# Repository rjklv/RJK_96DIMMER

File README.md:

# RJK_96DIMMER
Propeller based DMX 96 channel incandescent lamp dimmer

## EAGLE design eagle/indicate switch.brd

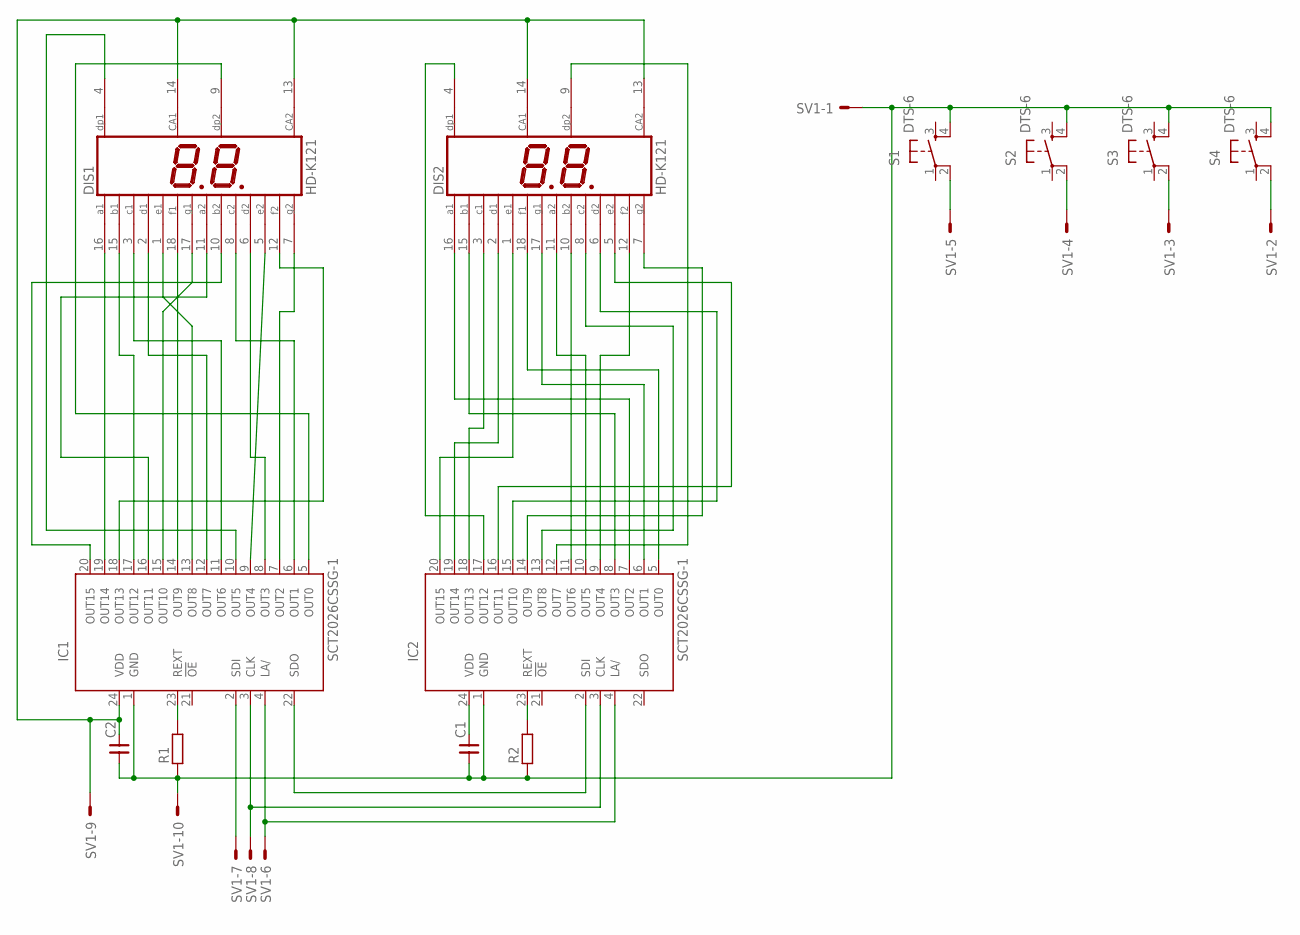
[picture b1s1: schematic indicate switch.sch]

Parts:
C1, C2: CNP-0805; 0805
DIS1, DIS2: HD-K121; HDSP-R
IC1, IC2: SCT2026CSSG-1; SSOP24
R1, R2: RESISTOR_0805; RESC2012X70N
S1, S2, S3, S4: DTS-6
SV1: ML10E; ML10

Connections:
unnamed: S2.2, SV1.4
unnamed: S1.2, SV1.5
unnamed: S4.2, SV1.2
unnamed: IC1.2 (SDI), SV1.7
unnamed: C1.1, C2.1, IC1.1 (GND), IC2.1 (GND), R1.1, R2.1, S1.4, S2.4, S3.4, S4.4, SV1.1, SV1.10
unnamed: C2.2, DIS1.13 (CA2), DIS1.14 (CA1), DIS2.13 (CA2), DIS2.14 (CA1), IC1.24 (VDD), SV1.9
unnamed: C1.2, IC2.24 (VDD)
unnamed: DIS1.15 (B1), IC1.17 (OUT12)
unnamed: IC1.23 (REXT), R1.2
unnamed: IC2.23 (REXT), R2.2
unnamed: S3.2, SV1.3
unnamed: IC1.3 (CLK), IC2.3 (CLK), SV1.8
unnamed: IC1.4 (LA/), IC2.4 (LA/), SV1.6
unnamed: IC1.22 (SDO), IC2.2 (SDI)
unnamed: DIS1.9 (DP2), IC1.5 (OUT0)
unnamed: DIS1.8 (C2), IC1.6 (OUT1)
unnamed: DIS1.7 (G2), IC1.7 (OUT2)
unnamed: DIS1.6 (D2), IC1.8 (OUT3)
unnamed: DIS1.5 (E2), IC1.9 (OUT4)
unnamed: DIS1.4 (DP1), IC1.10 (OUT5)
unnamed: DIS1.3 (C1), IC1.11 (OUT6)
unnamed: DIS1.2 (D1), IC1.12 (OUT7)
unnamed: DIS1.1 (E1), IC1.13 (OUT8)
unnamed: DIS1.18 (F1), IC1.14 (OUT9)
unnamed: DIS1.17 (G1), IC1.15 (OUT10)
unnamed: DIS1.16 (A1), IC1.16 (OUT11)
unnamed: DIS1.12 (F2), IC1.18 (OUT13)
unnamed: DIS1.11 (A2), IC1.19 (OUT14)
unnamed: DIS1.10 (B2), IC1.20 (OUT15)
unnamed: DIS2.18 (F1), IC2.5 (OUT0)
unnamed: DIS2.17 (G1), IC2.6 (OUT1)
unnamed: DIS2.16 (A1), IC2.7 (OUT2)
unnamed: DIS2.15 (B1), IC2.8 (OUT3)
unnamed: DIS2.12 (F2), IC2.9 (OUT4)
unnamed: DIS2.11 (A2), IC2.10 (OUT5)
unnamed: DIS2.10 (B2), IC2.11 (OUT6)
unnamed: DIS2.9 (DP2), IC2.12 (OUT7)
unnamed: DIS2.8 (C2), IC2.13 (OUT8)
unnamed: DIS2.7 (G2), IC2.14 (OUT9)
unnamed: DIS2.6 (D2), IC2.15 (OUT10)
unnamed: DIS2.5 (E2), IC2.16 (OUT11)
unnamed: DIS2.4 (DP1), IC2.17 (OUT12)
unnamed: DIS2.3 (C1), IC2.18 (OUT13)
unnamed: DIS2.2 (D1), IC2.19 (OUT14)
unnamed: DIS2.1 (E1), IC2.20 (OUT15)

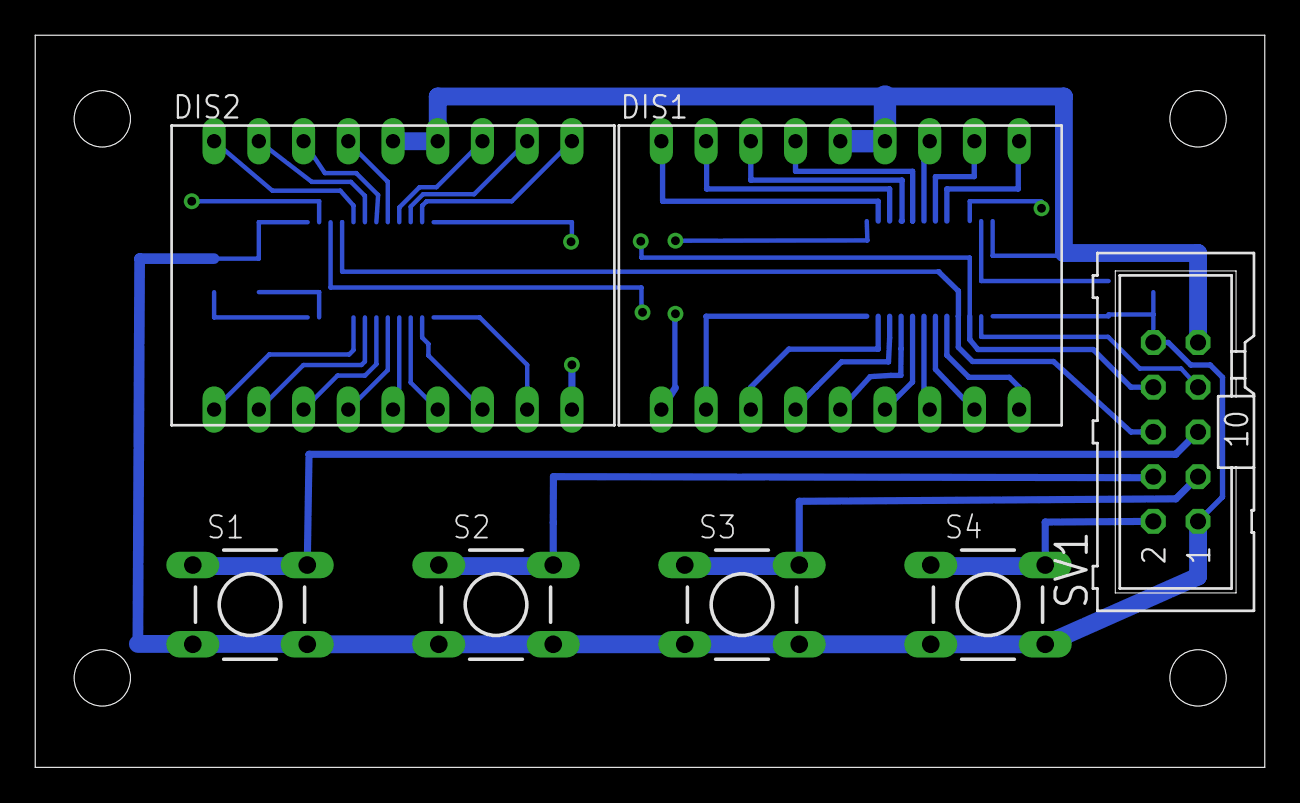
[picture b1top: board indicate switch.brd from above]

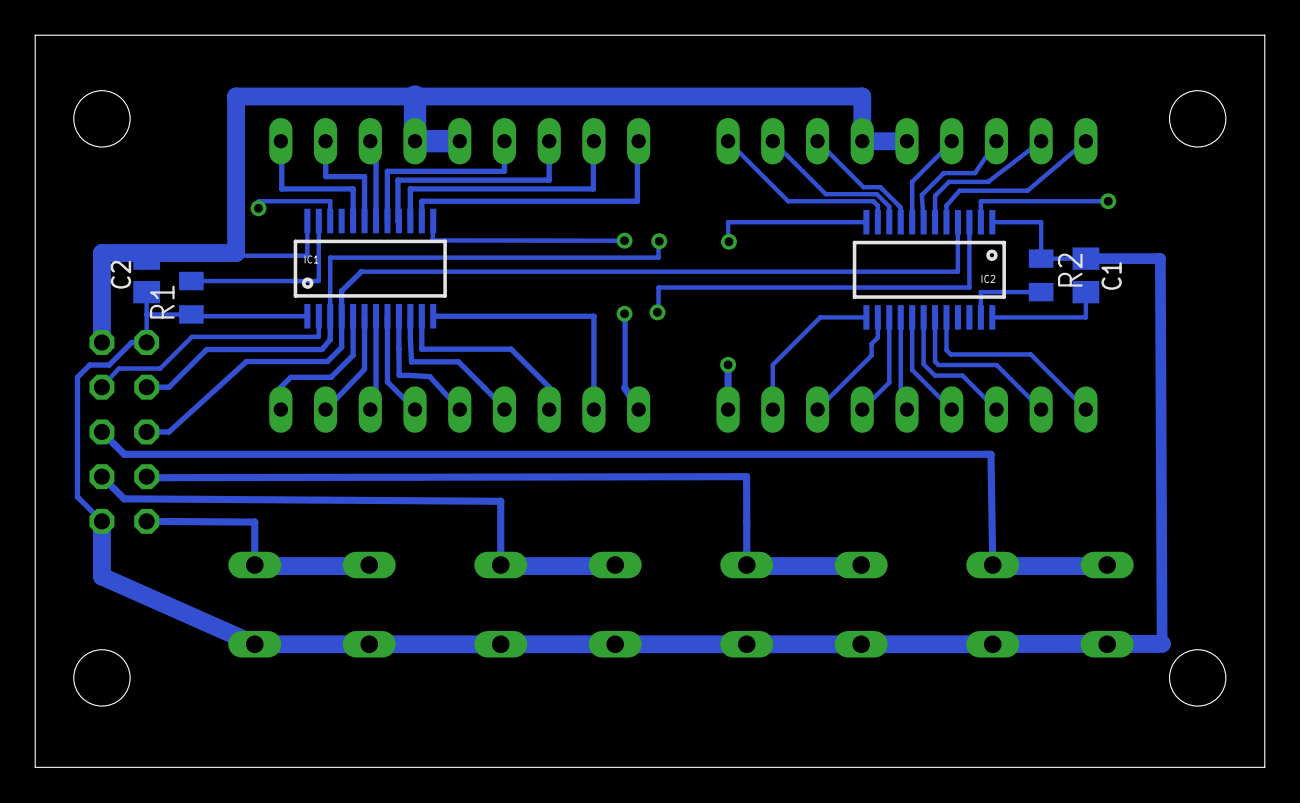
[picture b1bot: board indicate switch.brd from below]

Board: 2 copper layers, 69.8 x 41.6 mm, 13 parts (6 on the bottom side), 45 nets.

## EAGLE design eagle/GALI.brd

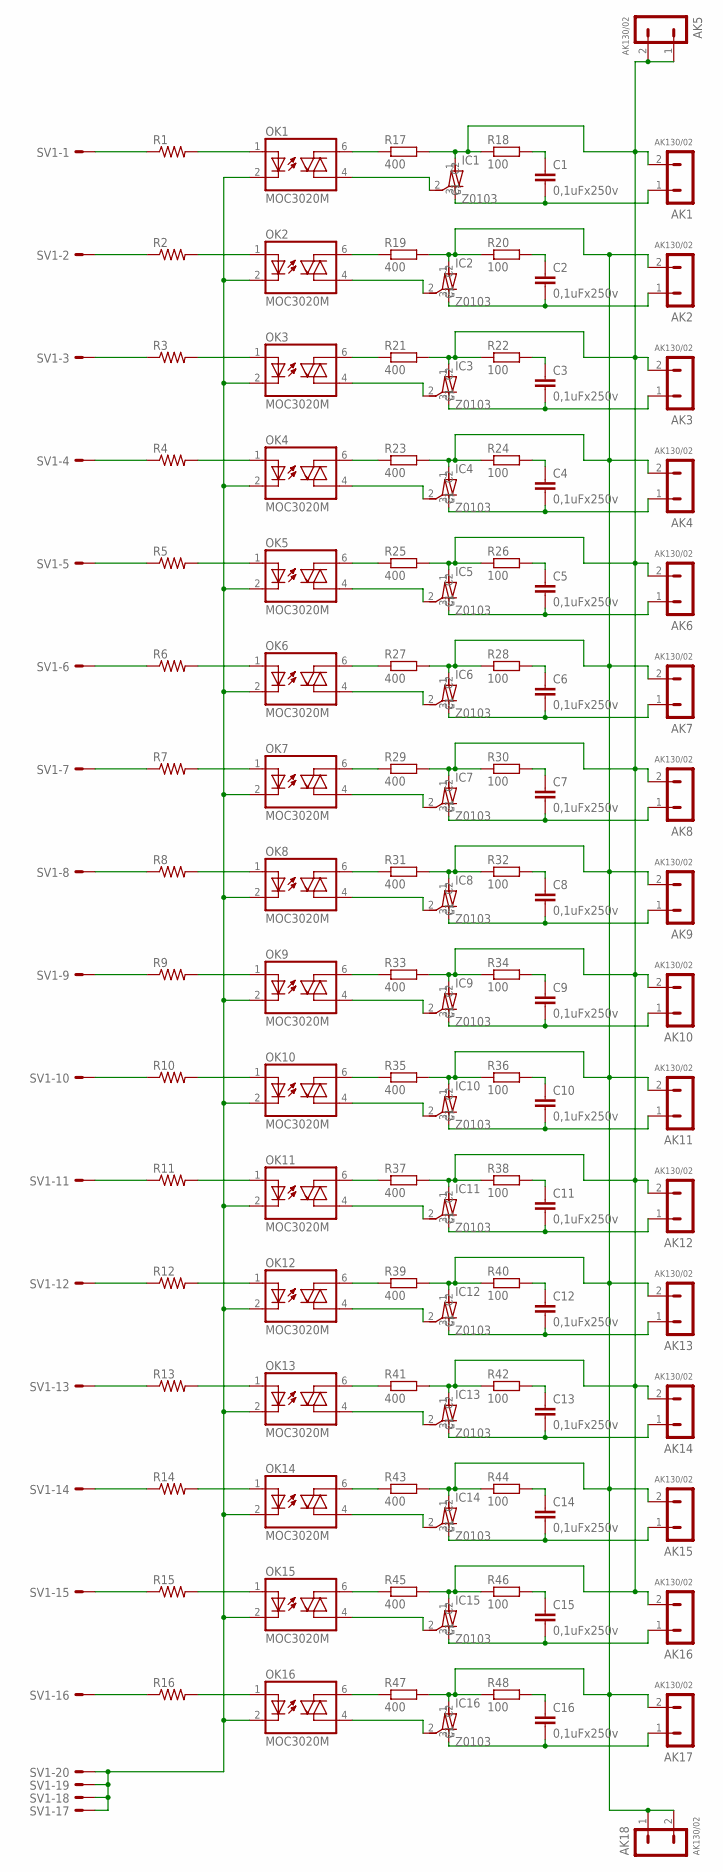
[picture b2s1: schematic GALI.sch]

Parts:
AK1, AK2, AK3, AK4, AK5, AK6, AK7, AK8, AK9, AK10, AK11, AK12, AK13, AK14, AK15, AK16, AK17, AK18: AK130/02; AK02
C1, C2, C3, C4, C5, C6, C7, C8, C9, C10, C11, C12, C13, C14, C15, C16: 0,1uFx250v; C102-054X133
IC1, IC2, IC3, IC4, IC5, IC6, IC7, IC8, IC9, IC10, IC11, IC12, IC13, IC14, IC15, IC16: Z0103; TO92-
OK1, OK2, OK3, OK4, OK5, OK6, OK7, OK8, OK9, OK10, OK11, OK12, OK13, OK14, OK15, OK16: MOC3020M; DIL06
R1, R2, R3, R4, R5, R6, R7, R8, R9, R10, R11, R12, R13, R14, R15, R16: R-US_0207/12; 0207/12
R17, R19, R21, R23, R25, R27, R29, R31, R33, R35, R37, R39, R41, R43, R45, R47: 400; P0613/15
R18, R20, R22, R24, R26, R28, R30, R32, R34, R36, R38, R40, R42, R44, R46, R48: 100; P0613/15
SV1: ML20E; ML20

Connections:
unnamed: R1.1, SV1.1
unnamed: OK2.1 (A), R2.2
unnamed: OK3.1 (A), R3.2
unnamed: OK4.1 (A), R4.2
unnamed: OK5.1 (A), R5.2
unnamed: OK6.1 (A), R6.2
unnamed: OK7.1 (A), R7.2
unnamed: OK8.1 (A), R8.2
unnamed: OK9.1 (A), R9.2
unnamed: OK10.1 (A), R10.2
unnamed: OK11.1 (A), R11.2
unnamed: OK12.1 (A), R12.2
unnamed: OK13.1 (A), R13.2
unnamed: OK14.1 (A), R14.2
unnamed: OK15.1 (A), R15.2
unnamed: R2.1, SV1.2
unnamed: OK1.2 (C), OK2.2 (C), OK3.2 (C), OK4.2 (C), OK5.2 (C), OK6.2 (C), OK7.2 (C), OK8.2 (C), OK9.2 (C), OK10.2 (C), OK11.2 (C), OK12.2 (C), OK13.2 (C), OK14.2 (C), OK15.2 (C), OK16.2 (C), SV1.17, SV1.18, SV1.19, SV1.20
unnamed: OK1.1 (A), R1.2
unnamed: R3.1, SV1.3
unnamed: R4.1, SV1.4
unnamed: R5.1, SV1.5
unnamed: R6.1, SV1.6
unnamed: R7.1, SV1.7
unnamed: R8.1, SV1.8
unnamed: R9.1, SV1.9
unnamed: R10.1, SV1.10
unnamed: R11.1, SV1.11
unnamed: R12.1, SV1.12
unnamed: R13.1, SV1.13
unnamed: R14.1, SV1.14
unnamed: R15.1, SV1.15
unnamed: R16.1, SV1.16
unnamed: OK16.1 (A), R16.2
unnamed: OK1.6 (A2), R17.1
unnamed: OK2.6 (A2), R19.1
unnamed: OK3.6 (A2), R21.1
unnamed: OK4.6 (A2), R23.1
unnamed: OK5.6 (A2), R25.1
unnamed: OK6.6 (A2), R27.1
unnamed: OK7.6 (A2), R29.1
unnamed: OK8.6 (A2), R31.1
unnamed: OK9.6 (A2), R33.1
unnamed: OK10.6 (A2), R35.1
unnamed: OK11.6 (A2), R37.1
unnamed: OK12.6 (A2), R39.1
unnamed: OK13.6 (A2), R41.1
unnamed: OK14.6 (A2), R43.1
unnamed: OK15.6 (A2), R45.1
unnamed: OK16.6 (A2), R47.1
unnamed: C3.1, R22.2
unnamed: IC1.2 (G), OK1.4 (A1)
unnamed: C2.1, R20.2
unnamed: IC2.2 (G), OK2.4 (A1)
unnamed: C1.1, R18.2
unnamed: IC3.2 (G), OK3.4 (A1)
unnamed: C6.1, R28.2
unnamed: IC4.2 (G), OK4.4 (A1)
unnamed: C5.1, R26.2
unnamed: IC5.2 (G), OK5.4 (A1)
unnamed: C4.1, R24.2
unnamed: IC6.2 (G), OK6.4 (A1)
unnamed: C7.1, R30.2
unnamed: IC7.2 (G), OK7.4 (A1)
unnamed: C8.1, R32.2
unnamed: IC8.2 (G), OK8.4 (A1)
unnamed: IC9.2 (G), OK9.4 (A1)
unnamed: AK1.2, AK3.2, AK5.1, AK5.2, AK6.2, AK8.2, AK10.2, AK12.2, AK14.2, AK16.2, IC1.1 (C1), IC3.1 (C1), IC5.1 (C1), IC7.1 (C1), IC9.1 (C1), IC11.1 (C1), IC13.1 (C1), IC15.1 (C1), R17.2, R18.1, R21.2, R22.1, R25.2, R26.1, R29.2, R30.1, R33.2, R34.1, R37.2, R38.1, R41.2, R42.1, R45.2, R46.1
unnamed: IC10.2 (G), OK10.4 (A1)
unnamed: IC11.2 (G), OK11.4 (A1)
unnamed: C10.1, R36.2
unnamed: IC12.2 (G), OK12.4 (A1)
unnamed: C14.1, R44.2
unnamed: IC13.2 (G), OK13.4 (A1)
unnamed: C13.1, R42.2
unnamed: IC14.2 (G), OK14.4 (A1)
unnamed: C15.1, R46.2
unnamed: IC15.2 (G), OK15.4 (A1)
unnamed: C16.1, R48.2
unnamed: IC16.2 (G), OK16.4 (A1)
unnamed: AK1.1, C1.2, IC1.3 (C2)
unnamed: AK2.1, C2.2, IC2.3 (C2)
unnamed: AK3.1, C3.2, IC3.3 (C2)
unnamed: AK4.1, C4.2, IC4.3 (C2)
unnamed: AK6.1, C5.2, IC5.3 (C2)
unnamed: AK7.1, C6.2, IC6.3 (C2)
unnamed: C11.1, R38.2
unnamed: AK8.1, C7.2, IC7.3 (C2)
unnamed: C12.1, R40.2
unnamed: AK9.1, C8.2, IC8.3 (C2)
unnamed: C9.1, R34.2
unnamed: AK10.1, C9.2, IC9.3 (C2)
unnamed: AK11.1, C10.2, IC10.3 (C2)
unnamed: AK12.1, C11.2, IC11.3 (C2)
unnamed: AK13.1, C12.2, IC12.3 (C2)
unnamed: AK14.1, C13.2, IC13.3 (C2)
unnamed: AK15.1, C14.2, IC14.3 (C2)
unnamed: AK16.1, C15.2, IC15.3 (C2)
unnamed: AK2.2, AK4.2, AK7.2, AK9.2, AK11.2, AK13.2, AK15.2, AK17.2, AK18.1, AK18.2, IC2.1 (C1), IC4.1 (C1), IC6.1 (C1), IC8.1 (C1), IC10.1 (C1), IC12.1 (C1), IC14.1 (C1), IC16.1 (C1), R19.2, R20.1, R23.2, R24.1, R27.2, R28.1, R31.2, R32.1, R35.2, R36.1, R39.2, R40.1, R43.2, R44.1, R47.2, R48.1
unnamed: AK17.1, C16.2, IC16.3 (C2)

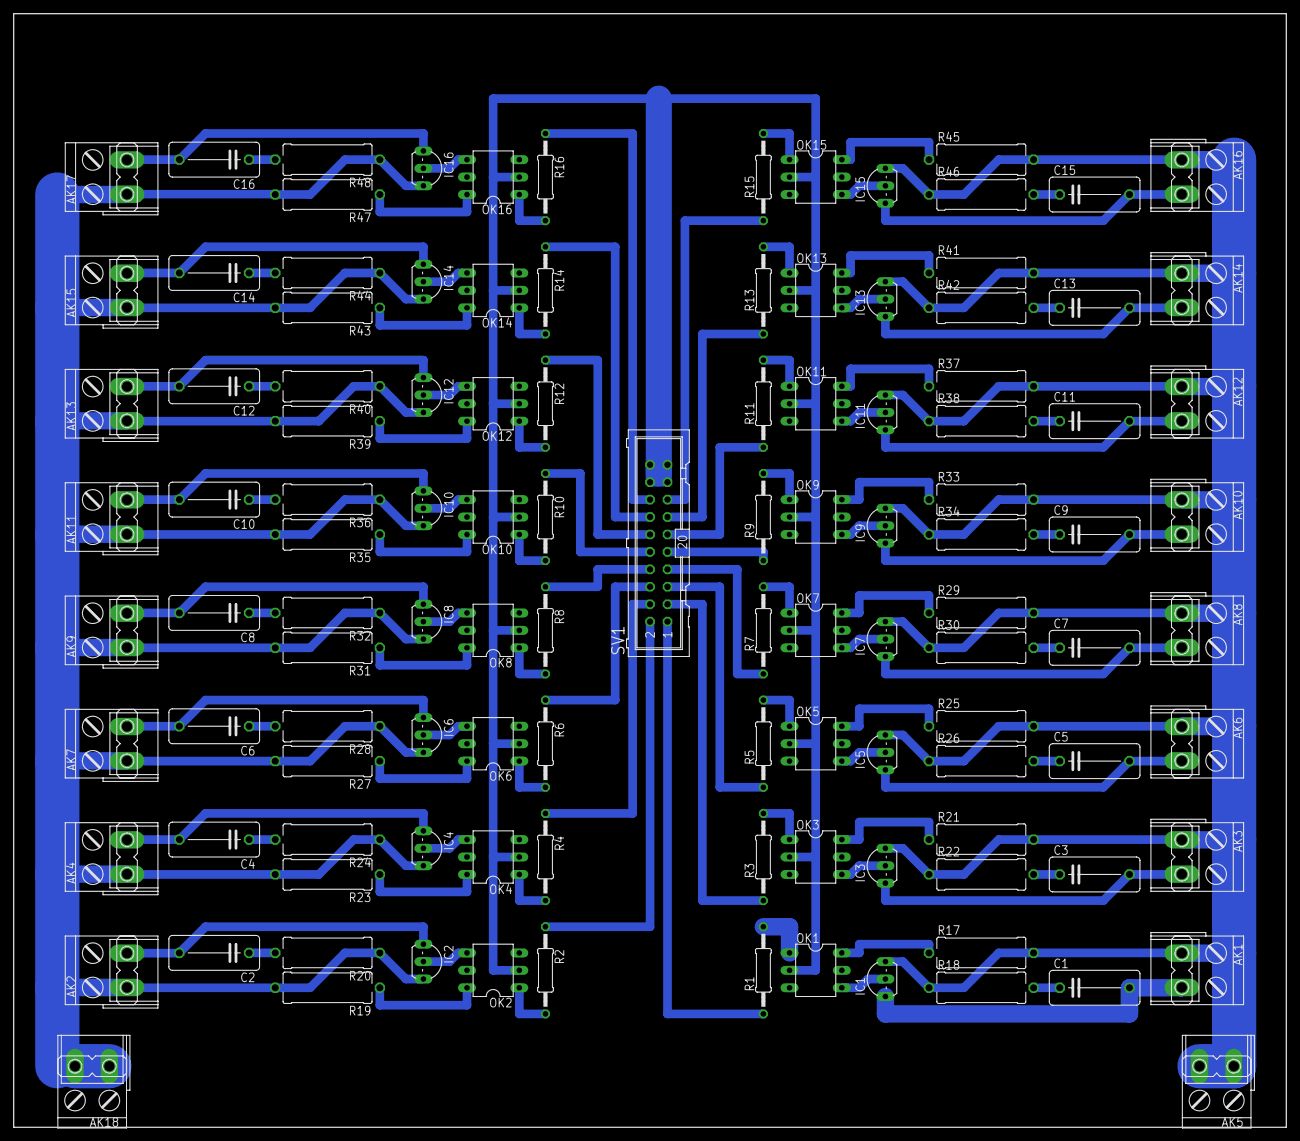
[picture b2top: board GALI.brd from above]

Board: 2 copper layers, 185.4 x 162.2 mm, 115 parts (0 on the bottom side), 99 nets.

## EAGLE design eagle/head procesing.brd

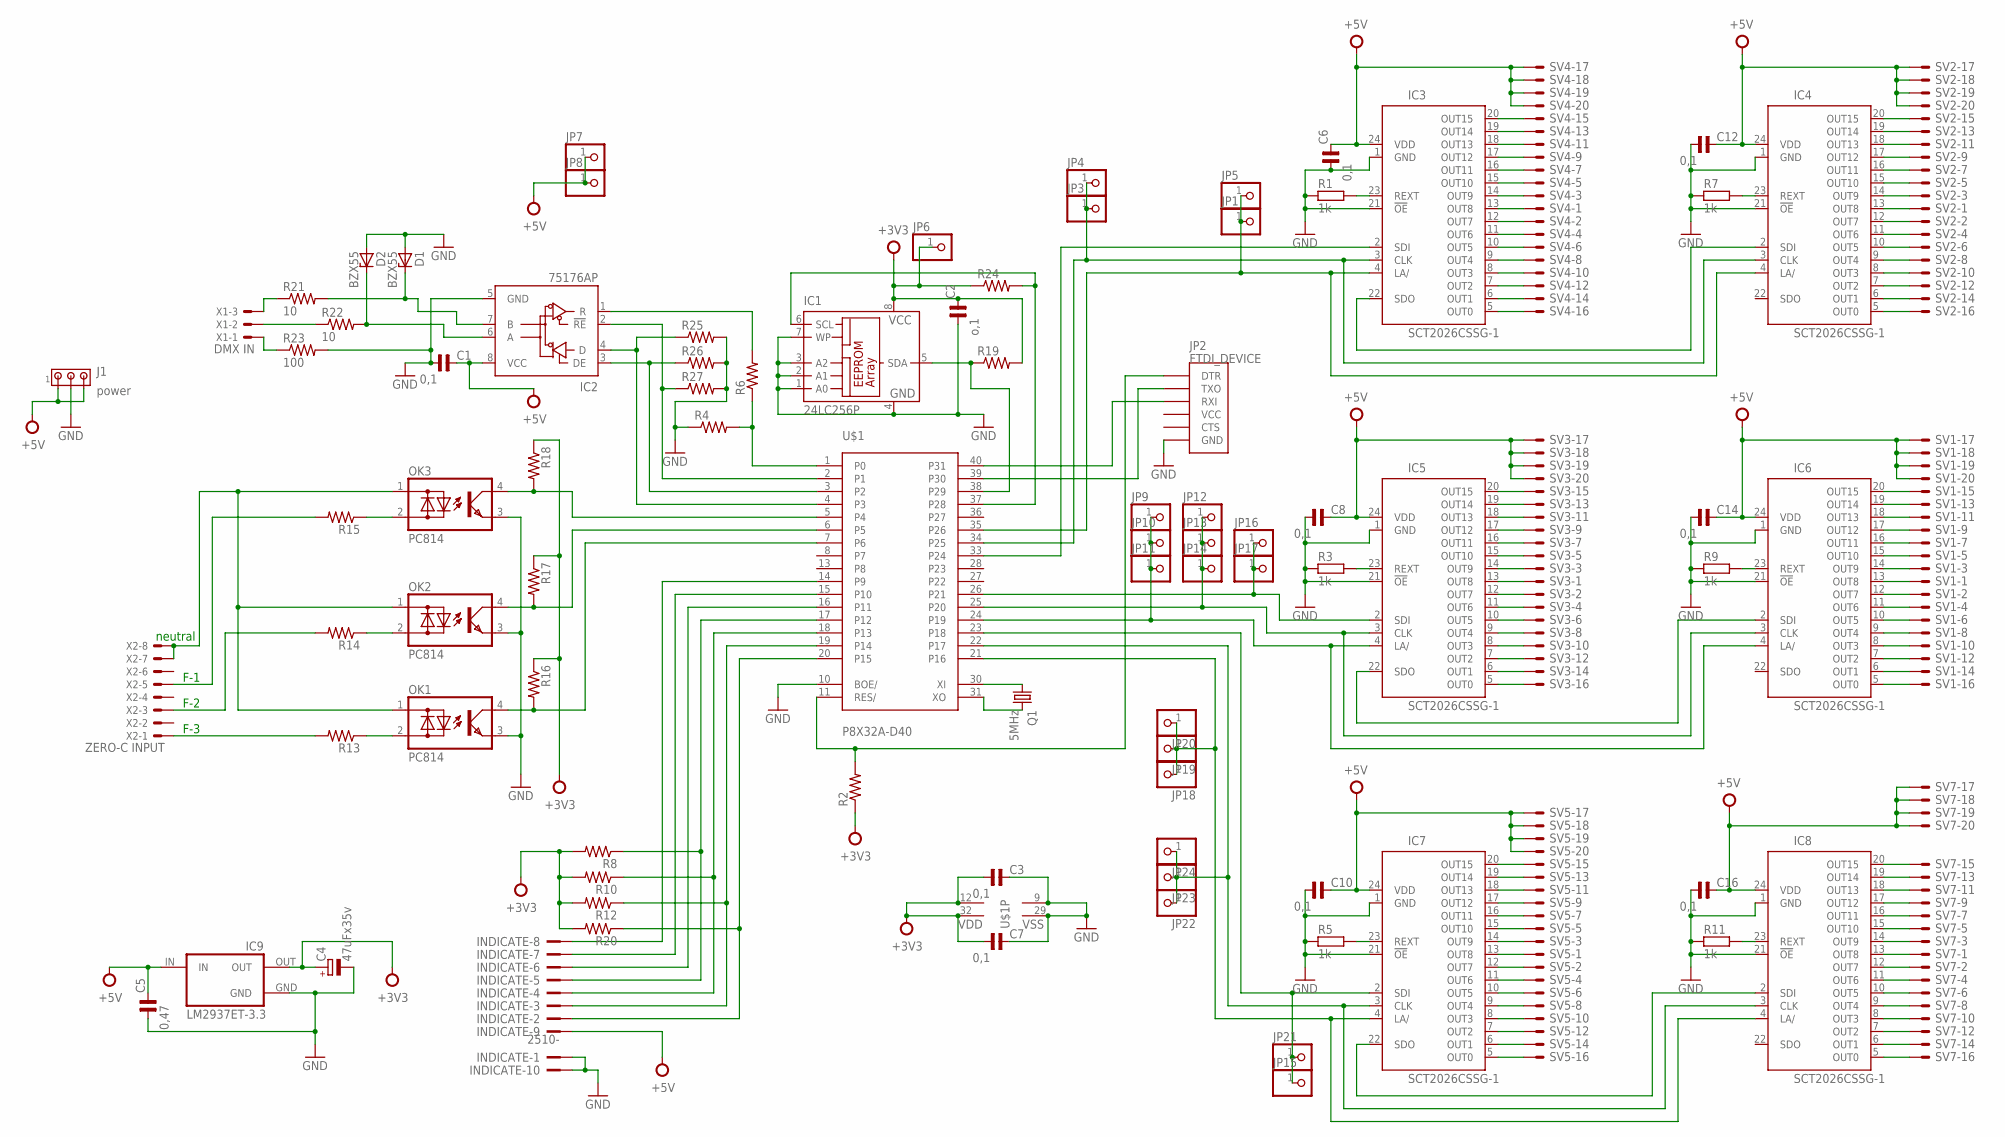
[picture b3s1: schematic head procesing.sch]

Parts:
C1, C3, C7: 0,1; C5,0-7,5X3,5
C2: o,1; C5,0-7,5X3,5
C4: 47uFx35v; E2-5
C5: 0,47; C5,0-7,5X3,5
C6, C8, C10, C12, C14, C16: 0,1; C-0805
D1, D2: BZX55; DO35Z10
IC1: 24LC256P; DIL8
IC2: 75176AP; DIL08
IC3, IC4, IC5, IC6, IC7, IC8: SCT2026CSSG-1; SSOP24
IC9: LM2937ET-3.3; TO220(V)
INDICATE: 2510-; PAK100/2500-10
J1: power; 350429-1
JP1, JP3, JP4, JP5, JP6, JP7, JP8, JP9, JP10, JP11, JP12, JP13, JP14, JP15, JP16, JP17, JP18, JP19, JP20, JP21, JP22, JP23, JP24: PINHD-1X1; 1X01
JP2: FTDI_DEVICE; FTDI_DEVICE_SIDE
OK1, OK2, OK3: PC814; DIL04
Q1: 5MHz; HC49U-V
R1, R3, R5, R7, R9, R11: 1k; RESC2012X70N
R2, R4, R6, R8, R10, R12, R13, R14, R15, R16, R17, R18, R19, R20, R24, R25, R26, R27: R-US_0207/10; 0207/10
R21, R22: 10; 0207/10
R23: 100; 0207/10
SV1, SV2, SV3, SV4, SV5, SV7: ML20E; ML20
U$1: P8X32A-D40
X1: DMX IN; 70543-03
X2: ZERO-C INPUT; 70543-08

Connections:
+3V3: C2.2, C3.1, C4.+, C7.1, IC1.8 (VCC), IC9.OUT, JP6.1, R2.1, R8.2, R10.2, R12.2, R16.1, R17.1, R18.1, R19.2, R20.2, R24.1, U$1.12 (VDD), U$1.32 (VDD)
+5V: C1.2, C5.2, C6.2, C8.2, C10.2, C12.2, C14.2, C16.2, IC2.8 (VCC), IC3.24 (VDD), IC4.24 (VDD), IC5.24 (VDD), IC6.24 (VDD), IC7.24 (VDD), IC8.24 (VDD), IC9.IN, INDICATE.9, J1.1, J1.3, JP7.1, JP8.1, SV1.17, SV1.18, SV1.19, SV1.20, SV2.17, SV2.18, SV2.19, SV2.20, SV3.17, SV3.18, SV3.19, SV3.20, SV4.17, SV4.18, SV4.19, SV4.20, SV5.17, SV5.18, SV5.19, SV5.20, SV7.17, SV7.18, SV7.19, SV7.20
CLK: INDICATE.8, U$1.14 (P9)
GND: C1.1, C2.1, C3.2, C4.-, C5.1, C6.1, C7.2, C8.1, C10.1, C12.1, C14.1, C16.1, D1.A, D2.A, IC1.1 (A0), IC1.2 (A1), IC1.3 (A2), IC1.4 (GND), IC1.7 (WP), IC2.5 (GND), IC3.1 (GND), IC3.21 (!OE), IC4.1 (GND), IC4.21 (!OE), IC5.1 (GND), IC5.21 (!OE), IC6.1 (GND), IC6.21 (!OE), IC7.1 (GND), IC7.21 (!OE), IC8.1 (GND), IC8.21 (!OE), IC9.GND, INDICATE.1, INDICATE.10, J1.2, JP2.P$6 (GND), OK1.3 (E), OK2.3 (E), OK3.3 (E), R1.1, R3.1, R4.1, R5.1, R7.1, R9.1, R11.1, R23.2, R25.2, R26.2, R27.2, U$1.9 (VSS), U$1.10 (BOE/), U$1.29 (VSS)
LA/: INDICATE.6, U$1.16 (P11)
unnamed: OK1.4 (C), R16.2, U$1.7 (P6)
unnamed: OK2.4 (C), R17.2, U$1.6 (P5)
unnamed: OK3.4 (C), R18.2, U$1.5 (P4)
unnamed: OK3.2 (AC2), R15.1
unnamed: R15.2, X2.5
unnamed: IC2.3 (DE), R26.1, U$1.3 (P2)
unnamed: OK2.2 (AC2), R14.1
unnamed: R14.2, X2.3
unnamed: OK1.1 (AC1), OK2.1 (AC1), OK3.1 (AC1), X2.7, X2.8
unnamed: IC3.20 (OUT15), SV4.15
unnamed: OK1.2 (AC2), R13.1
unnamed: R13.2, X2.1
unnamed: IC3.3 (CLK), IC4.3 (CLK), JP3.1, JP4.1, U$1.34 (P25)
unnamed: IC3.23 (REXT), R1.2
unnamed: IC3.19 (OUT14), SV4.13
unnamed: D2.C, IC2.6 (A), R22.2
unnamed: D1.C, IC2.7 (B), R21.2
unnamed: R4.2, R6.1, U$1.1 (P0)
unnamed: IC3.18 (OUT13), SV4.11
unnamed: IC5.23 (REXT), R3.2
unnamed: IC3.17 (OUT12), SV4.9
unnamed: IC4.23 (REXT), R7.2
unnamed: IC3.16 (OUT11), SV4.7
unnamed: IC6.23 (REXT), R9.2
unnamed: IC3.15 (OUT10), SV4.5
unnamed: IC3.2 (SDI), U$1.33 (P24)
unnamed: IC7.23 (REXT), R5.2
unnamed: IC3.14 (OUT9), SV4.3
unnamed: IC3.4 (LA/), IC4.4 (LA/), JP1.1, JP5.1, U$1.35 (P26)
unnamed: IC8.23 (REXT), R11.2
unnamed: IC5.4 (LA/), IC6.4 (LA/), JP9.1, JP10.1, JP11.1, U$1.24 (P19)
unnamed: IC3.13 (OUT8), SV4.1
unnamed: IC3.12 (OUT7), SV4.2
unnamed: IC3.11 (OUT6), SV4.4
unnamed: IC1.5 (SDA), R19.1, U$1.38 (P29)
unnamed: IC1.6 (SCL), R24.2, U$1.37 (P28)
unnamed: Q1.1, U$1.30 (XI)
unnamed: IC5.3 (CLK), IC6.3 (CLK), JP12.1, JP13.1, JP14.1, U$1.25 (P20)
unnamed: IC5.2 (SDI), JP16.1, JP17.1, U$1.26 (P21)
unnamed: IC3.22 (SDO), IC4.2 (SDI)
unnamed: IC7.2 (SDI), JP15.1, JP21.1, U$1.23 (P18)
unnamed: IC7.3 (CLK), IC8.3 (CLK), JP22.1, JP23.1, JP24.1, U$1.22 (P17)
unnamed: IC5.22 (SDO), IC6.2 (SDI)
unnamed: IC7.22 (SDO), IC8.2 (SDI)
unnamed: IC4.20 (OUT15), SV2.15
unnamed: IC6.20 (OUT15), SV1.15
unnamed: IC6.19 (OUT14), SV1.13
unnamed: IC6.18 (OUT13), SV1.11
unnamed: IC6.17 (OUT12), SV1.9
unnamed: IC6.16 (OUT11), SV1.7
unnamed: IC6.15 (OUT10), SV1.5
unnamed: IC6.14 (OUT9), SV1.3
unnamed: IC6.13 (OUT8), SV1.1
unnamed: IC6.12 (OUT7), SV1.2
unnamed: IC6.11 (OUT6), SV1.4
unnamed: IC6.10 (OUT5), SV1.6
unnamed: IC6.9 (OUT4), SV1.8
unnamed: IC6.8 (OUT3), SV1.10
unnamed: IC6.7 (OUT2), SV1.12
unnamed: IC6.6 (OUT1), SV1.14
unnamed: IC6.5 (OUT0), SV1.16
unnamed: IC4.19 (OUT14), SV2.13
unnamed: IC4.18 (OUT13), SV2.11
unnamed: IC4.17 (OUT12), SV2.9
unnamed: IC4.16 (OUT11), SV2.7
unnamed: IC4.15 (OUT10), SV2.5
unnamed: IC4.14 (OUT9), SV2.3
unnamed: IC4.13 (OUT8), SV2.1
unnamed: IC4.12 (OUT7), SV2.2
unnamed: IC4.11 (OUT6), SV2.4
unnamed: IC4.10 (OUT5), SV2.6
unnamed: IC4.9 (OUT4), SV2.8
unnamed: IC4.8 (OUT3), SV2.10
unnamed: IC4.7 (OUT2), SV2.12
unnamed: IC4.6 (OUT1), SV2.14
unnamed: IC4.5 (OUT0), SV2.16
unnamed: IC3.10 (OUT5), SV4.6
unnamed: IC7.20 (OUT15), SV5.15
unnamed: IC7.19 (OUT14), SV5.13
unnamed: IC7.18 (OUT13), SV5.11
unnamed: IC7.17 (OUT12), SV5.9
unnamed: IC7.16 (OUT11), SV5.7
unnamed: IC7.15 (OUT10), SV5.5
unnamed: IC7.14 (OUT9), SV5.3
unnamed: IC7.13 (OUT8), SV5.1
unnamed: IC7.12 (OUT7), SV5.2
unnamed: IC7.11 (OUT6), SV5.4
unnamed: IC7.10 (OUT5), SV5.6
unnamed: IC7.9 (OUT4), SV5.8
unnamed: IC7.8 (OUT3), SV5.10
unnamed: IC7.7 (OUT2), SV5.12
unnamed: IC7.6 (OUT1), SV5.14
unnamed: IC7.5 (OUT0), SV5.16
unnamed: IC8.20 (OUT15), SV7.15
unnamed: IC3.9 (OUT4), SV4.8
unnamed: IC5.20 (OUT15), SV3.15
unnamed: IC8.19 (OUT14), SV7.13
unnamed: IC8.18 (OUT13), SV7.11
unnamed: IC8.17 (OUT12), SV7.9
unnamed: IC8.16 (OUT11), SV7.7
unnamed: IC8.15 (OUT10), SV7.5
unnamed: IC8.14 (OUT9), SV7.3
unnamed: IC8.13 (OUT8), SV7.1
unnamed: IC8.12 (OUT7), SV7.2
unnamed: IC8.11 (OUT6), SV7.4
unnamed: IC8.10 (OUT5), SV7.6
unnamed: IC8.9 (OUT4), SV7.8
unnamed: IC8.8 (OUT3), SV7.10
unnamed: IC8.7 (OUT2), SV7.12
unnamed: IC8.6 (OUT1), SV7.14
unnamed: IC8.5 (OUT0), SV7.16
unnamed: IC5.19 (OUT14), SV3.13
unnamed: IC5.18 (OUT13), SV3.11
unnamed: IC5.17 (OUT12), SV3.9
unnamed: IC5.16 (OUT11), SV3.7
unnamed: IC5.15 (OUT10), SV3.5
unnamed: IC5.14 (OUT9), SV3.3
unnamed: IC5.13 (OUT8), SV3.1
unnamed: IC5.12 (OUT7), SV3.2
unnamed: IC5.11 (OUT6), SV3.4
unnamed: IC5.10 (OUT5), SV3.6
unnamed: IC5.9 (OUT4), SV3.8
unnamed: IC5.8 (OUT3), SV3.10
unnamed: IC5.7 (OUT2), SV3.12
unnamed: IC5.6 (OUT1), SV3.14
unnamed: IC5.5 (OUT0), SV3.16
unnamed: IC3.8 (OUT3), SV4.10
unnamed: IC3.7 (OUT2), SV4.12
unnamed: IC3.6 (OUT1), SV4.14
unnamed: IC3.5 (OUT0), SV4.16
unnamed: Q1.2, U$1.31 (XO)
unnamed: JP2.P$1 (DTR), R2.2, U$1.11 (RES/)
unnamed: IC7.4 (LA/), IC8.4 (LA/), JP18.1, JP19.1, JP20.1, U$1.21 (P16)
unnamed: JP2.P$2 (TXO), U$1.39 (P30)
unnamed: JP2.P$3 (RXI), U$1.40 (P31)
unnamed: IC2.1 (R), R6.2
unnamed: IC2.2 (!RE), R27.1, U$1.2 (P1)
unnamed: IC2.4 (D), R25.1, U$1.4 (P3)
unnamed: R23.1, X1.1
unnamed: R21.1, X1.3
unnamed: R22.1, X1.2
S1-MENU: INDICATE.5, R8.1, U$1.17 (P12)
S2-UP: INDICATE.4, R10.1, U$1.18 (P13)
S3-DOWN: INDICATE.3, R12.1, U$1.19 (P14)
S4-ENTER: INDICATE.2, R20.1, U$1.20 (P15)
SDI: INDICATE.7, U$1.15 (P10)

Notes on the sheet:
neutral
F-1
F-2
F-3

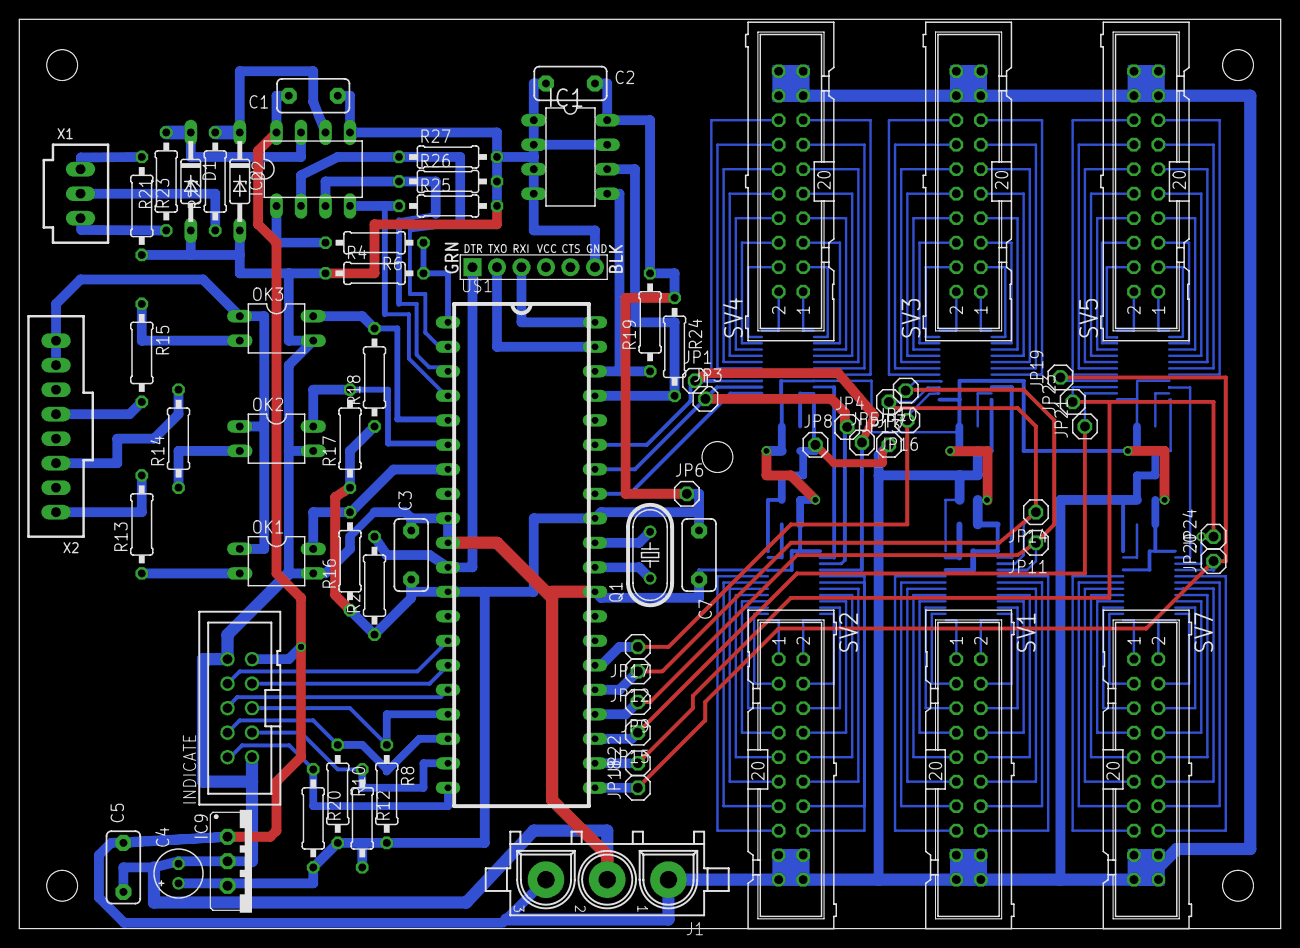
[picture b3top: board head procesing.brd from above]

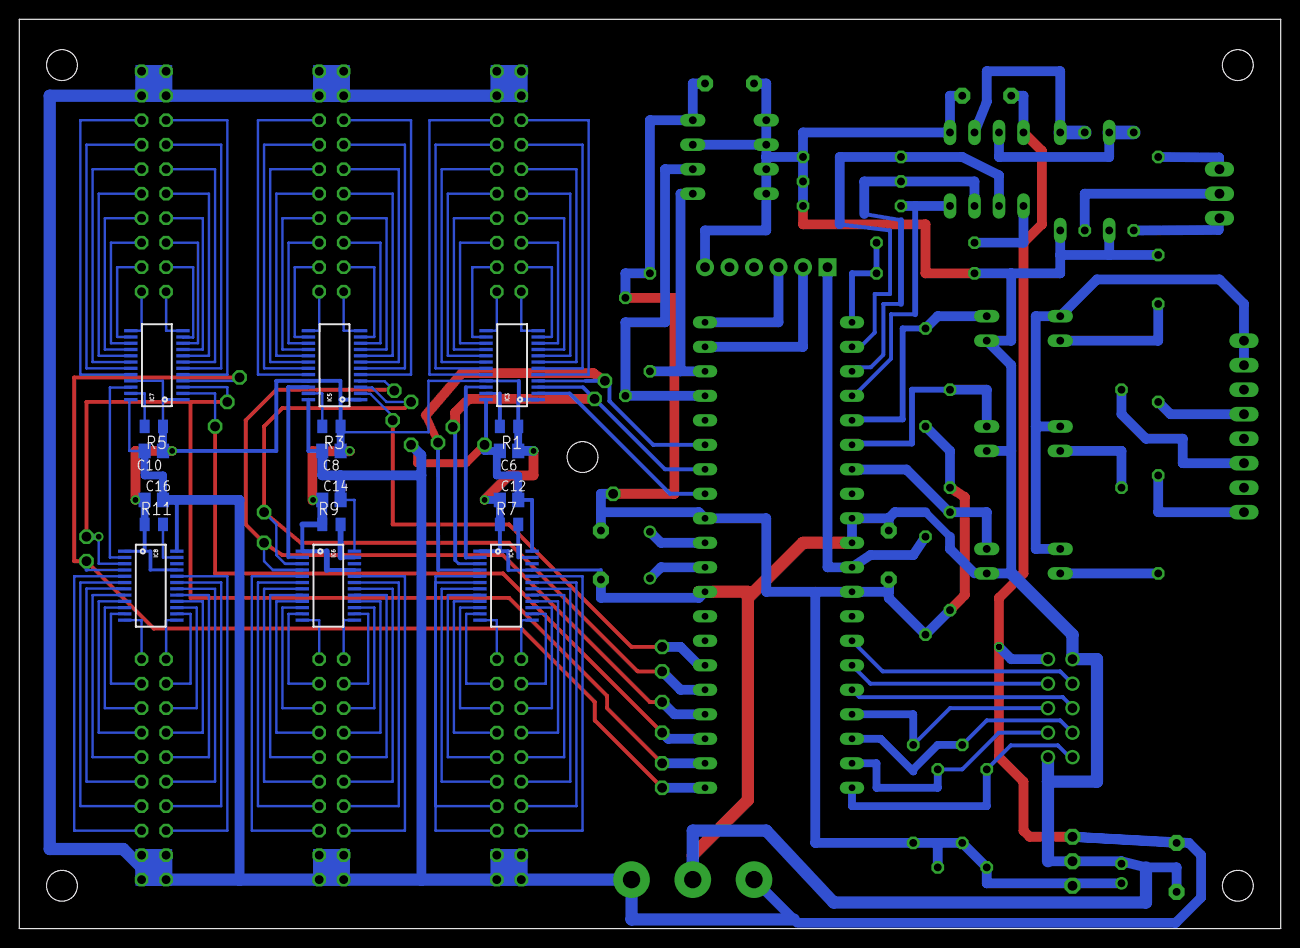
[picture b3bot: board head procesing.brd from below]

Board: 2 copper layers, 130.8 x 94.3 mm, 89 parts (18 on the bottom side), 151 nets.

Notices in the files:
parts and their libraries:
cap-pan40: Copyright (C) 2004, Bob Starr
SparkFun-Connectors: Licensing: Creative Commons ShareAlike 4.0 International - https://creativecommons.org/licenses/by-sa/4.0
